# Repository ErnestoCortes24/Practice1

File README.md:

# Practice 1. Developiong the PCB (Schematic)

## Objectives

The student will make the schematic design of a minimum card system, which he/she will work with throughout the semester. The minimum system contains following elements: potentiometer and thermistor ICs, serial port, power connector, LCD , push buttons,  LEDs, and keyboard connections. The students will use the design software ‘Kicad’ for the entire design (schematic and layout.)

## Introduction

Microcontrollers are all around  he world. Each day, Microcontrollers, are more present in the many aspects of our lives: in our work, inside our houses, and in more. We can find them controlling small devices like cellphones, microwaves, washing machines, and televisions.

A microcontroller is one device or chip that is used to govern one or more processes. For example, the controller that regulates the room temperature of an air conditioner; it has a sensor that continuously measures the internal temperature and, when the preset limits are exceeded, it generates the necessary signals to adjust the temperature.

## State of the Art

### The practices and the PIC microcontroller

The main objective of this practices is to provide students the foundation to fully understand the operation of the PIC18F45K50 microcontroller. This will be achieved through 11 documents that will guide the reader to create their own electronic card or Printed Circuit Board (PCB) and to be able to program it; in order to, execute different functions.

The advantages of ta PIC microcontroller to others on the market, which is why it will be used throughout this manual, are as follows:

- Easy to operate.
- There is enough documentation to work with it and it’s easy to obtain it.
- The price is comparatively lower than its competitors.
- It has a high operating speed.
- Development tools are cheap and easy to use.
- There are a variety of hardware that can record, erase and check the behavior of PIC.
- Once you learn to handle a PIC, it will easier to handle any other models of microcontrollers.

### KiCad EDA Software

KiCad is an open source software suite for Electronic Design Automation (EDA). The programs handle Schematic Capture,
and PCB Layout with Gerber output. The suite runs on Windows, Linux and macOS and is licensed under GNU GPL v3. The
first release date was in 1992 by its original author, Jean-Pierre Charras, but is now currently under development by
the KiCad Developers Team. 

## Results

In this section, you must report the outcomes of the laboratory activities.

### Follow the next 'Project Configuration' Steps

1. Download and install the open source (free) software ‘KiCad EDA’ form its official [web page](https://kicad-pcb.org/).  
2. Click on ‘kicad.exe’ application. Now, you are in the main window: ‘Kicad Project Manager,’ as shown in Fig. 1. From here, you will be capable of accessing 5 different tools: EESchema, Cvpcb, PCBnew, GerbView and Bitmpa2Component.

3. Create a new project: **File→New→Project… [CTRL + N]**. Open the project folder, all files in your project will be saved there. The project will be saved with the ‘.pro’ extension. 
***NOTE:*** *Make sure that the PATH of your project does not include special characters like “spaces, accentuations, letter ‘ñ’, etc.”*
4. Begin to create the schematic. Let us open the EESchema editor, It is the first button on the left of the ‘Project Manager.’ If a dialog message pops, select: *‘Create an empty symbol library table…’*.
5. Click the icon **‘Page Settings’**  located in the top of the toolbar. Select the size ‘A3’ and enter the title of your schematic. You can see there is more information that can be provided if necessary. Once completed the necessary information, click **‘OK.’** This information will appear in the lower right corner of the design page. 
6. Download from this repository the libraries needed for the project. Add all the libraries into **'KiCad': Preferences
   -> Manage Symbol Libraries ...** Click on ***'Project Specific Libraries...'*** tab. Nextr, click on the button
   **'Browse Libraries...'** and search for the folder where you save the libraries. Select all the libaries and click
   **'OK'**.
7. Now let's add      dd the first component of the design. Click the iceon ‘Place symbol’  in the toolbar on the right.
   The same functionality is obtained by pressing the shortcut [Shift + A]. If a warning message pops, ignore it and
   click ‘OK.’ The component selection window appears. *NOTE: You can see a list of all availabe shortcut by pressing [Ctrl + F1].*
8. Select with a click on the ‘+ symbol’ the library ‘device.’ Here you have a list of all available components in the library ‘device,’ which is the one that contains the most commonly used components.
9. Scroll down and click the resistance ‘R.’ This action will close the component selection window and take you back to the schematic sheet.
10. Place the component in the schematic by clicking wherever you want it to be. You can zoom in or out the ‘scroll’ of your mouse.
11. With the mouse over the ‘R’ component, press the key [R]. You will see how the component rotates 90°; you do not need to click on the component to rotate it.
12. Click on the middle of the component and select: Properties→Edit value... You can get the same result on the component by positioning the curse above it and pressing the key [V]. Also with the key [E], you will have a window with the more general properties. When you click the right mouse button on the component, all the possible ‘shortcut keys’ actions will appear.
13. The value of the component appears. Replace the current value ‘R’ for ‘1k’ and click ‘OK.’ Do not modify the reference field (R?), this option is automatically modified later. The value inside the resistor should now be ‘1k,’.
14. If you made a mistake and want to delete a component, you must right-click the mouse on the component and select ‘Delete.’ This action will delete the component from the schematic. Also, you can delete it by pressing the key [Del] and hovering the mouse over it.
15. You can duplicate an existing component in your schematic by positioning the cursor on the component and pressing the key [C]. Then, click on the wanted position to place the new component.
16. Press right click on the resistance. Select ‘Drag.’ Reposition the component and left click to drop it. The same function can be done by clicking the key [G]. You can use the key [R] to rotate the component. NOTE: The right-click option ‘Move X’ (equivalent to key [M]) is a viable option to move any compenent, but is used for components that have not been connected.
17. To add the symbols +5V and GND (reference), select the button ‘Place a power port’  in the toolbar located in the right. You may also use the shortcut key [A] on the datasheet and select the ‘power’ library.
18. This is also the same procedure to add +5VA (+5V alternative) and GNDA (alternative reference). In your PCB design will be the two different types of power: direct and alternative. You need to be careful in adding each type of power on your design.
19. To wire the components, you must click on the icon ‘Place a wire’  located in the toolbar on the right. NOTE: Be careful not to select the ‘Place a bus’ below this button. The use of that button will be explained later.
20. Sometimes it is good to give names to the wires using ‘labels’ which is an alternative form of wiring connections between components. To do this, you must click on the icon ‘Place net label’  in the toolbar on the right. You can also press the command [Shift + L]. Sometimes, ‘labels’ are used only for purposes of information on one line.
21. The non-connected terminals must be identified to avoid errors or warnings in the schematic. To mark a connections that will be free, you must select the icon ‘Place no connection flag’  located in the toolbar on the right, and place the ‘X’ symbol on the free terminal.
22. It is necessary to add ‘Power Flags’ to signal ‘KiCad’ that the power comes from a valid source. Press key [A], double click on the ‘power’ library and search for a ‘PWR_FLAG’ .
23. Sometimes it is good to write comments or notes in the schematic. To do so, you can select: Place→Graphic Text… You can also press the command [Shift + T].

### Create the Schematic of our PCB design

24. Now, it is time to assemble the schematic design needed to make the PCB of this manual, as shown in this
    [file](./Minimum_card_system.pdf). Table I indicates in which library is included each component.

25. All components must have a unique identifier. In fact, many of the added components are named after ‘R?’ or ‘J?.’ To assign an ID automatically, you can click on the icon ‘Annote schematic symbols’ .
26. In the window ‘Annotate Schematic’ select: Use the entire schematic and click on the ‘Annotate’ button. Click ‘OK’ in the confirmation message that appears on the screen, then click on ‘Close.’ You will see how all the ‘?’ have been replaced by numbers. This identifier is unique.

### Check and Prepare our PCB design

27.  Now let’s check the schematic for error(s). Click the icon ‘Perform Electrical Rules Check’ . Click the ‘Run’ button. A report informing you of any error, warning and/or disconnected terminals will appear. You should have 0 errors and 0 warnings. If any of the cases, a green arrow appears in the schematic positioned where the error or warning exists. For further information about the errors, select on Create ERC file report and then press ‘Run.’ 
28. The schematic is finished. Now we can create a ‘Netlist file’ that will be added to the impression of each component. Click on the icon ‘Generate Netlist’  located in the toolbar on the top. Click on ‘Generate Netlist’ and then ‘Save.’ Save it with the name that appears by default.
29. Now you may close the schematic editor.

### Report
For this practice, modify only the Conclusion section. Commit an push the changes on the fork of this repository and add
upload the link on Canvas.

### File uploads
Commit and push the files with extensions .pro, .sch, and .net created once you completed all the steps of the document
in forked repository.

### Demonstration
Screenshot the image of the complete schematic and upload it at the repository.

## Conclusion

In this section, you should add the conclusions, suggestions, and/or problems of the laboratory activities. Each team member must add his/her own conclusion (5 lines as minimum for each member).# Practice 1. Developiong the PCB (Schematic)

## Objectives

The student will make the schematic design of a minimum card system, which he/she will work with throughout the semester. The minimum system contains following elements: potentiometer and thermistor ICs, serial port, power connector, LCD , push buttons,  LEDs, and keyboard connections. The students will use the design software ‘Kicad’ for the entire design (schematic and layout.)

## Introduction

Microcontrollers are all around  he world. Each day, Microcontrollers, are more present in the many aspects of our lives: in our work, inside our houses, and in more. We can find them controlling small devices like cellphones, microwaves, washing machines, and televisions.

A microcontroller is one device or chip that is used to govern one or more processes. For example, the controller that regulates the room temperature of an air conditioner; it has a sensor that continuously measures the internal temperature and, when the preset limits are exceeded, it generates the necessary signals to adjust the temperature.

## State of the Art

### The practices and the PIC microcontroller

The main objective of this practices is to provide students the foundation to fully understand the operation of the PIC18F45K50 microcontroller. This will be achieved through 11 documents that will guide the reader to create their own electronic card or Printed Circuit Board (PCB) and to be able to program it; in order to, execute different functions.

The advantages of ta PIC microcontroller to others on the market, which is why it will be used throughout this manual, are as follows:

- Easy to operate.
- There is enough documentation to work with it and it’s easy to obtain it.
- The price is comparatively lower than its competitors.
- It has a high operating speed.
- Development tools are cheap and easy to use.
- There are a variety of hardware that can record, erase and check the behavior of PIC.
- Once you learn to handle a PIC, it will easier to handle any other models of microcontrollers.

### KiCad EDA Software

KiCad is an open source software suite for Electronic Design Automation (EDA). The programs handle Schematic Capture,
and PCB Layout with Gerber output. The suite runs on Windows, Linux and macOS and is licensed under GNU GPL v3. The
first release date was in 1992 by its original author, Jean-Pierre Charras, but is now currently under development by
the KiCad Developers Team. 

## Results

In this section, you must report the outcomes of the laboratory activities.

### Follow the next 'Project Configuration' Steps

1. Download and install the open source (free) software ‘KiCad EDA’ form its official [web page](https://kicad-pcb.org/).  
2. Click on ‘kicad.exe’ application. Now, you are in the main window: ‘Kicad Project Manager,’ as shown in Fig. 1. From here, you will be capable of accessing 5 different tools: EESchema, Cvpcb, PCBnew, GerbView and Bitmpa2Component.

3. Create a new project: **File→New→Project… [CTRL + N]**. Open the project folder, all files in your project will be saved there. The project will be saved with the ‘.pro’ extension. 
***NOTE:*** *Make sure that the PATH of your project does not include special characters like “spaces, accentuations, letter ‘ñ’, etc.”*
4. Begin to create the schematic. Let us open the EESchema editor, It is the first button on the left of the ‘Project Manager.’ If a dialog message pops, select: *‘Create an empty symbol library table…’*.
5. Click the icon **‘Page Settings’**  located in the top of the toolbar. Select the size ‘A3’ and enter the title of your schematic. You can see there is more information that can be provided if necessary. Once completed the necessary information, click **‘OK.’** This information will appear in the lower right corner of the design page. 
6. Download from this repository the libraries needed for the project. Add all the libraries into **'KiCad': Preferences
   -> Manage Symbol Libraries ...** Click on ***'Project Specific Libraries...'*** tab. Nextr, click on the button
   **'Browse Libraries...'** and search for the folder where you save the libraries. Select all the libaries and click
   **'OK'**.
7. Now let's add      dd the first component of the design. Click the iceon ‘Place symbol’  in the toolbar on the right.
   The same functionality is obtained by pressing the shortcut [Shift + A]. If a warning message pops, ignore it and
   click ‘OK.’ The component selection window appears. *NOTE: You can see a list of all availabe shortcut by pressing [Ctrl + F1].*
8. Select with a click on the ‘+ symbol’ the library ‘device.’ Here you have a list of all available components in the library ‘device,’ which is the one that contains the most commonly used components.
9. Scroll down and click the resistance ‘R.’ This action will close the component selection window and take you back to the schematic sheet.
10. Place the component in the schematic by clicking wherever you want it to be. You can zoom in or out the ‘scroll’ of your mouse.
11. With the mouse over the ‘R’ component, press the key [R]. You will see how the component rotates 90°; you do not need to click on the component to rotate it.
12. Click on the middle of the component and select: Properties→Edit value... You can get the same result on the component by positioning the curse above it and pressing the key [V]. Also with the key [E], you will have a window with the more general properties. When you click the right mouse button on the component, all the possible ‘shortcut keys’ actions will appear.
13. The value of the component appears. Replace the current value ‘R’ for ‘1k’ and click ‘OK.’ Do not modify the reference field (R?), this option is automatically modified later. The value inside the resistor should now be ‘1k,’.
14. If you made a mistake and want to delete a component, you must right-click the mouse on the component and select ‘Delete.’ This action will delete the component from the schematic. Also, you can delete it by pressing the key [Del] and hovering the mouse over it.
15. You can duplicate an existing component in your schematic by positioning the cursor on the component and pressing the key [C]. Then, click on the wanted position to place the new component.
16. Press right click on the resistance. Select ‘Drag.’ Reposition the component and left click to drop it. The same function can be done by clicking the key [G]. You can use the key [R] to rotate the component. NOTE: The right-click option ‘Move X’ (equivalent to key [M]) is a viable option to move any compenent, but is used for components that have not been connected.
17. To add the symbols +5V and GND (reference), select the button ‘Place a power port’  in the toolbar located in the right. You may also use the shortcut key [A] on the datasheet and select the ‘power’ library.
18. This is also the same procedure to add +5VA (+5V alternative) and GNDA (alternative reference). In your PCB design will be the two different types of power: direct and alternative. You need to be careful in adding each type of power on your design.
19. To wire the components, you must click on the icon ‘Place a wire’  located in the toolbar on the right. NOTE: Be careful not to select the ‘Place a bus’ below this button. The use of that button will be explained later.
20. Sometimes it is good to give names to the wires using ‘labels’ which is an alternative form of wiring connections between components. To do this, you must click on the icon ‘Place net label’  in the toolbar on the right. You can also press the command [Shift + L]. Sometimes, ‘labels’ are used only for purposes of information on one line.
21. The non-connected terminals must be identified to avoid errors or warnings in the schematic. To mark a connections that will be free, you must select the icon ‘Place no connection flag’  located in the toolbar on the right, and place the ‘X’ symbol on the free terminal.
22. It is necessary to add ‘Power Flags’ to signal ‘KiCad’ that the power comes from a valid source. Press key [A], double click on the ‘power’ library and search for a ‘PWR_FLAG’ .
23. Sometimes it is good to write comments or notes in the schematic. To do so, you can select: Place→Graphic Text… You can also press the command [Shift + T].

### Create the Schematic of our PCB design

24. Now, it is time to assemble the schematic design needed to make the PCB of this manual, as shown in this
    [file](./Minimum_card_system.pdf). Table I indicates in which library is included each component.

25. All components must have a unique identifier. In fact, many of the added components are named after ‘R?’ or ‘J?.’ To assign an ID automatically, you can click on the icon ‘Annote schematic symbols’ .
26. In the window ‘Annotate Schematic’ select: Use the entire schematic and click on the ‘Annotate’ button. Click ‘OK’ in the confirmation message that appears on the screen, then click on ‘Close.’ You will see how all the ‘?’ have been replaced by numbers. This identifier is unique.

### Check and Prepare our PCB design

27.  Now let’s check the schematic for error(s). Click the icon ‘Perform Electrical Rules Check’ . Click the ‘Run’ button. A report informing you of any error, warning and/or disconnected terminals will appear. You should have 0 errors and 0 warnings. If any of the cases, a green arrow appears in the schematic positioned where the error or warning exists. For further information about the errors, select on Create ERC file report and then press ‘Run.’ 
28. The schematic is finished. Now we can create a ‘Netlist file’ that will be added to the impression of each component. Click on the icon ‘Generate Netlist’  located in the toolbar on the top. Click on ‘Generate Netlist’ and then ‘Save.’ Save it with the name that appears by default.
29. Now you may close the schematic editor.

### Report
For this practice, modify only the Conclusion section. Commit an push the changes on the fork of this repository and add
upload the link on Canvas.

### File uploads
Commit and push the files with extensions .pro, .sch, and .net created once you completed all the steps of the document
in forked repository.

### Demonstration
Screenshot the image of the complete schematic and upload it at the repository.

## Conclusion
I can tell in this practice I could learned to use KiCad. First, the difference between a PSpice and a PCB creator is the libraries that you need to put. I mean, the libraries that you have to put to create a desired circuit. Among enything else is the same.
In this case, all the components were added in a A3 sheet with Pots, LCDs, MAX 232, PushButtons, power supply, Leds and matrix keyboard. I just added the components required and conect with wires.  
Finally, something that I didn't understand is why the components are separated. I think, in base with this components will create a PCB module, and I don't undertand why.

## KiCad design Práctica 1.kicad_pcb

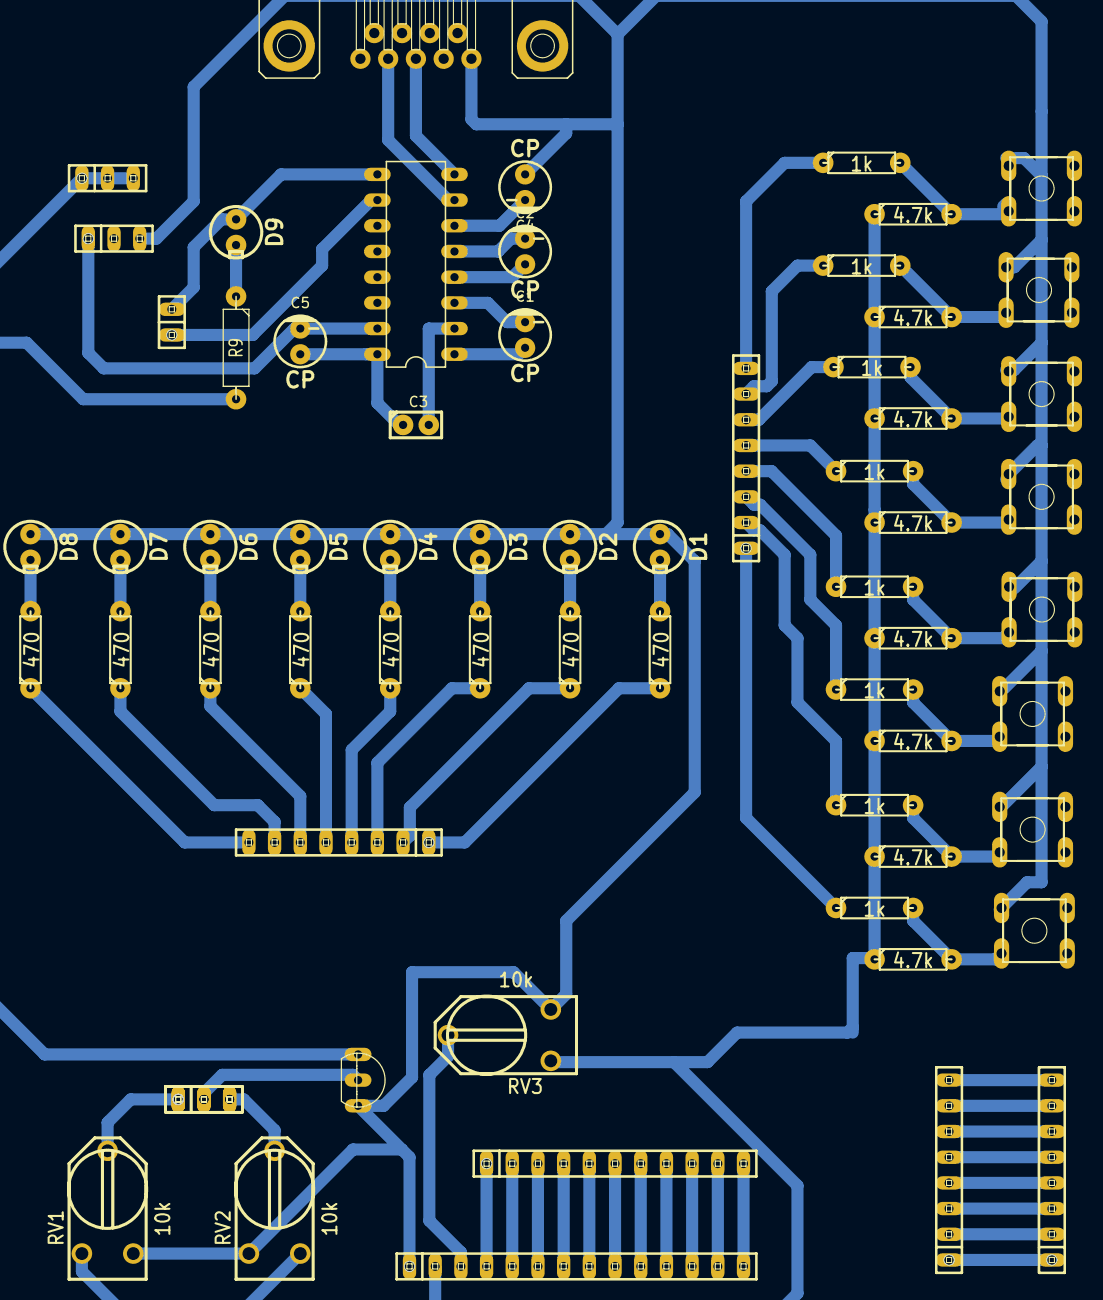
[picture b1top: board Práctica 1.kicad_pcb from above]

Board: 2 copper layers, 64 parts (0 on the bottom side), 69 nets.

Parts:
C1, C2, C4, C5: CP; Capacitor_elect
C3: CP; Capacitor
D1, D2, D3, D4, D5, D6, D7, D8, D9: LED; Led
JP1, JP2, JP3, JP3#2: PINHD-1X3; pinhead-1X03
JP4, JP8, JP9, JP10: PINHD-1X8M; pinhead-1X08
JP5: PINHD-1X14M; pinhead-1X14
JP6: PINHD-1X11M; pinhead-1X11
JP7: PINHD-1X2; pinhead-1X02
R1, R2, R3, R4, R5, R6, R7, R8: 470; Resistor
R9: 470; Resistor_large
R10, R11, R12, R13, R14, R15, R16, R17: 1k; Resistor
R18, R19, R20, R21, R22, R23, R24, R25: 4.7k; Resistor
RV1, RV2, RV3: 10k; RV2X4
S1, S2, S3, S4, S5, S6, S7, S8: DTS-6
U1: MCP9700A
U2: MAX232; Maxim232
X1: F09HP; Conector_F09HP

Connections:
+5VA: JP2.1, JP2.2, JP2.3, JP5.2, R9.2, R18.1, R19.1, R20.1, R21.1, R22.1, R23.1, R24.1, R25.1, RV1.1, RV2.3, RV3.1, U1.1
GNDA: C4.1, C5.2, D1.1, D2.1, D3.1, D4.1, D5.1, D6.1, D7.1, D8.1, JP1.1, JP1.2, JP1.3, JP5.1, RV1.3, RV2.1, RV3.3, S1.1, S2.1, S3.1, S4.1, S5.1, S6.1, S7.1, S8.1, U1.3, U2.15, X1.5
unnamed: C1.1, U2.1
unnamed: C1.2, U2.3
unnamed: C2.1, U2.4
unnamed: C2.2, U2.5
unnamed: C3.1, C5.1, U2.16
unnamed: C3.2, U2.2
unnamed: C4.2, U2.6
unnamed: D1.2, R1.2
unnamed: D2.2, R2.2
unnamed: D3.2, R3.2
unnamed: D4.2, R4.2
unnamed: D5.2, R5.2
unnamed: D6.2, R6.2
unnamed: D7.2, R7.2
unnamed: D8.2, R8.2
unnamed: D9.1, JP7.2, U2.9
unnamed: D9.2, R9.1
unnamed: JP3.1, JP3#2.1, RV1.2
unnamed: JP3.2, JP3#2.2, U1.2
unnamed: JP3.3, JP3#2.3, RV2.2
unnamed: JP4.1, R1.1
unnamed: JP4.2, R2.1
unnamed: JP4.3, R3.1
unnamed: JP4.4, R4.1
unnamed: JP4.5, R5.1
unnamed: JP4.6, R6.1
unnamed: JP4.7, R7.1
unnamed: JP4.8, R8.1
unnamed: JP5.3, RV3.2
unnamed: JP5.4, JP6.1
unnamed: JP5.5, JP6.2
unnamed: JP5.6, JP6.3
unnamed: JP5.7, JP6.4
unnamed: JP5.8, JP6.5
unnamed: JP5.9, JP6.6
unnamed: JP5.10, JP6.7
unnamed: JP5.11, JP6.8
unnamed: JP5.12, JP6.9
unnamed: JP5.13, JP6.10
unnamed: JP5.14, JP6.11
unnamed: JP7.1, U2.10
unnamed: JP8.1, R10.1
unnamed: JP8.2, R11.1
unnamed: JP8.3, R12.1
unnamed: JP8.4, R13.1
unnamed: JP8.5, R14.1
unnamed: JP8.6, R15.1
unnamed: JP8.7, R16.1
unnamed: JP8.8, R17.1
unnamed: JP9.1, JP10.1
unnamed: JP9.2, JP10.2
unnamed: JP9.3, JP10.3
unnamed: JP9.4, JP10.4
unnamed: JP9.5, JP10.5
unnamed: JP9.6, JP10.6
unnamed: JP9.7, JP10.7
unnamed: JP9.8, JP10.8
unnamed: R10.2, R18.2, S1.3
unnamed: R11.2, R19.2, S2.3
unnamed: R12.2, R20.2, S3.3
unnamed: R13.2, R21.2, S4.3
unnamed: R14.2, R22.2, S5.3
unnamed: R15.2, R23.2, S6.3
unnamed: R16.2, R24.2, S7.3
unnamed: R17.2, R25.2, S8.3
unnamed: U2.7, X1.2
unnamed: U2.8, X1.3
